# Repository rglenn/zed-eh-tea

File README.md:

# rg-rc2014
My own experiments in RC2014 hardware

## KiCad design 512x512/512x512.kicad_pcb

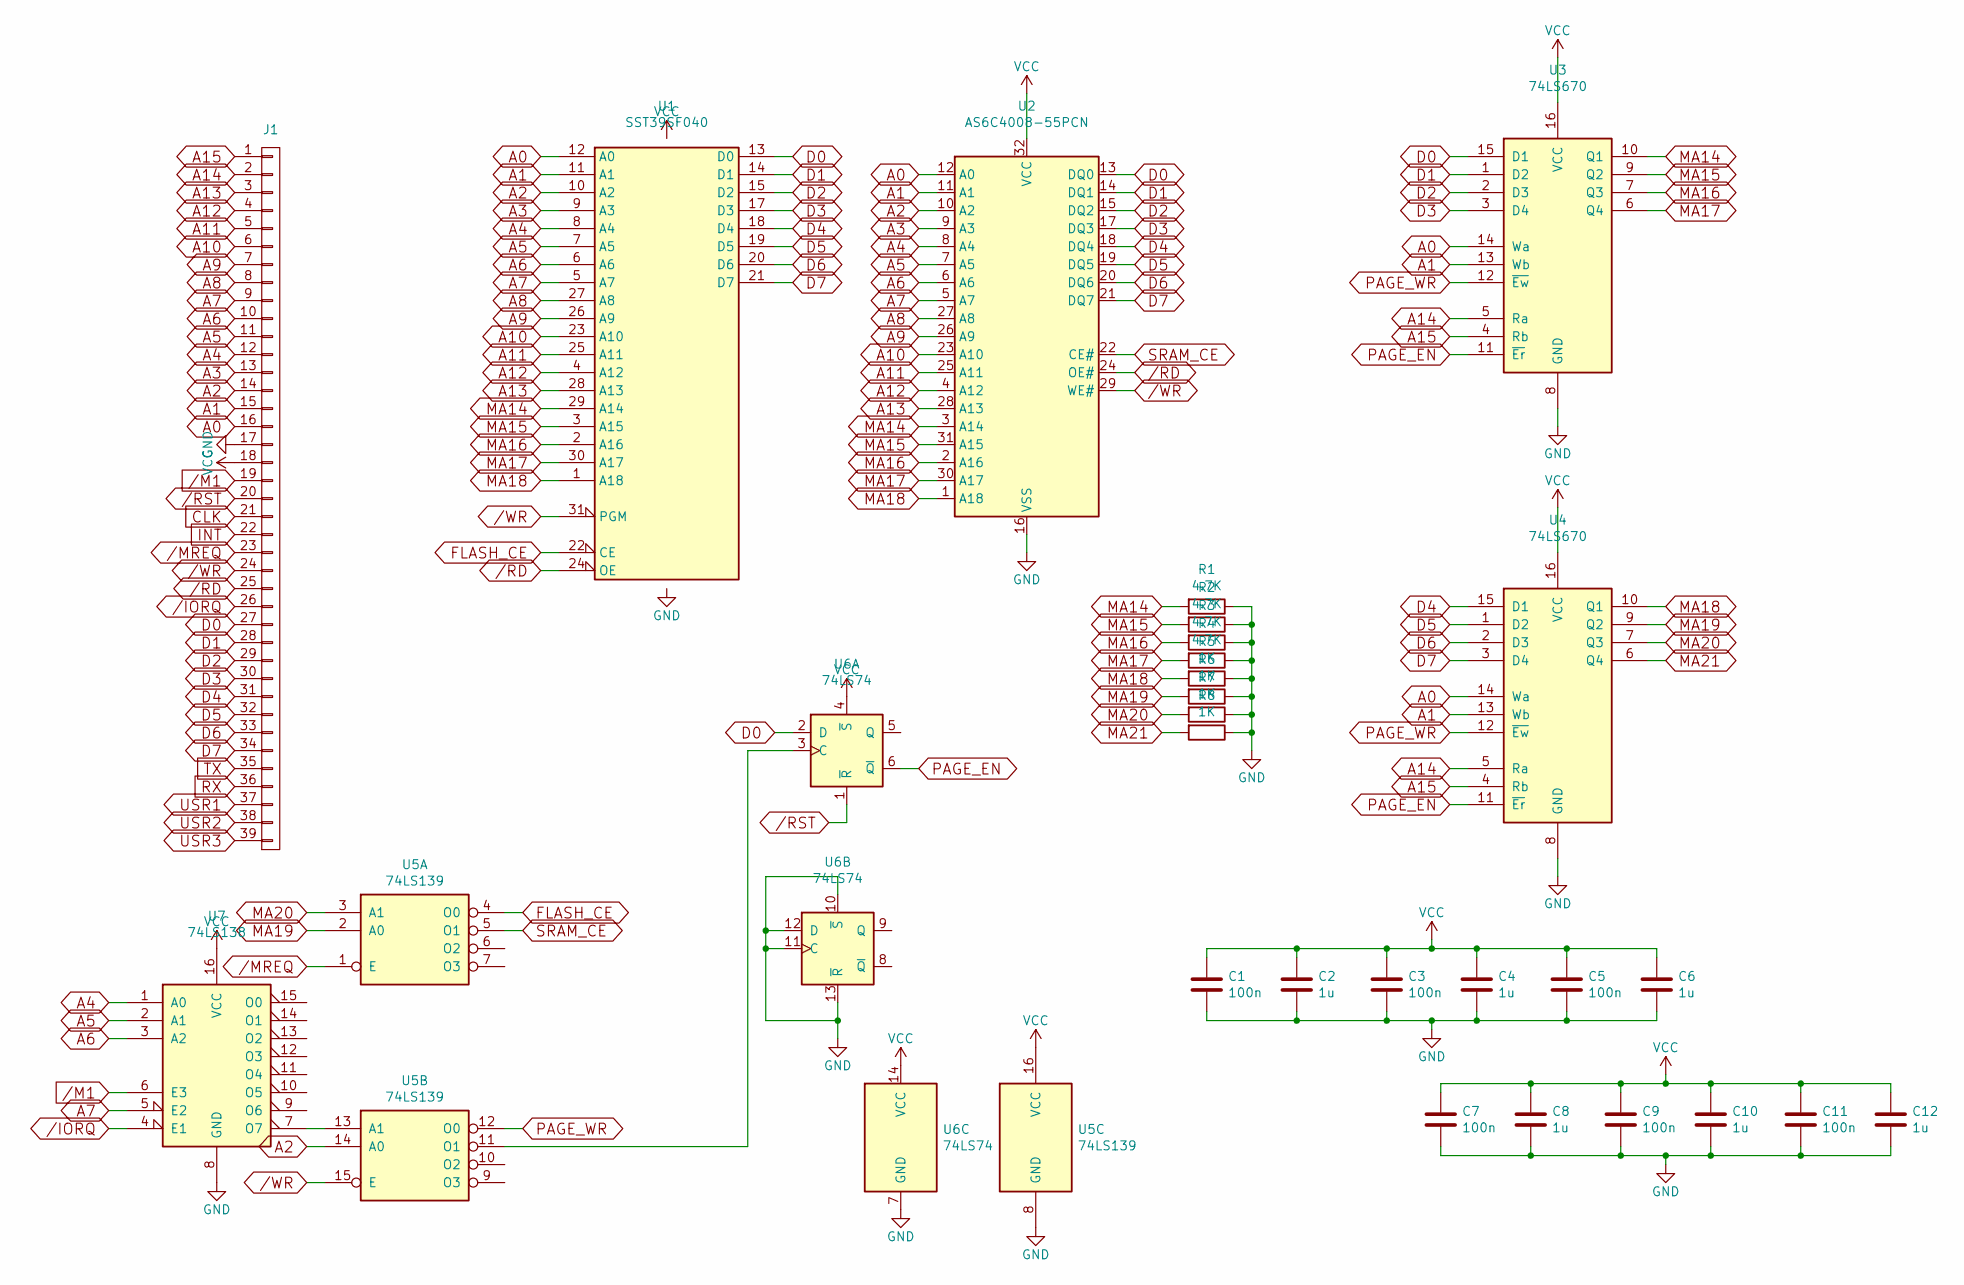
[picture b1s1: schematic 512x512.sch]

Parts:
C1, C3, C5, C7, C9, C11: 100n; C_0603_1608Metric
C2, C4, C6, C8, C10, C12: 1u; C_0603_1608Metric
J1: CONN_01X39; Pin_Header_Straight_1x39_Pitch2.54mm
R1, R2, R3, R4: 4.7K; R_Axial_DIN0204_L3.6mm_D1.6mm_P7.62mm_Horizontal
R5, R6, R7, R8: 1K; R_Axial_DIN0204_L3.6mm_D1.6mm_P7.62mm_Horizontal
U1: SST39SF040; DIP-32_W15.24mm
U2: AS6C4008-55PCN; DIP-32_W15.24mm
U3, U4: 74LS670; DIP-16_W7.62mm
U5: 74LS139; DIP-16_W7.62mm
U6: 74LS74; DIP-14_W7.62mm
U7: 74LS138; DIP-16_W7.62mm

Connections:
/IORQ: J1.26, U7.4 (E1)
/M1: J1.19, U7.6 (E3)
/MREQ: J1.23, U5.1 (E)
/RD: J1.25, U1.24 (OE), U2.24 (OE#)
/RST: J1.20, U6.1 (~R)
/WR: J1.24, U1.31 (PGM), U2.29 (WE#), U5.15 (E)
A0: J1.16, U1.12 (A0), U2.12 (A0), U3.14 (Wa), U4.14 (Wa)
A1: J1.15, U1.11 (A1), U2.11 (A1), U3.13 (Wb), U4.13 (Wb)
A2: J1.14, U1.10 (A2), U2.10 (A2), U5.14 (A0)
A3: J1.13, U1.9 (A3), U2.9 (A3)
A4: J1.12, U1.8 (A4), U2.8 (A4), U7.1 (A0)
A5: J1.11, U1.7 (A5), U2.7 (A5), U7.2 (A1)
A6: J1.10, U1.6 (A6), U2.6 (A6), U7.3 (A2)
A7: J1.9, U1.5 (A7), U2.5 (A7), U7.5 (E2)
A8: J1.8, U1.27 (A8), U2.27 (A8)
A9: J1.7, U1.26 (A9), U2.26 (A9)
A10: J1.6, U1.23 (A10), U2.23 (A10)
A11: J1.5, U1.25 (A11), U2.25 (A11)
A12: J1.4, U1.4 (A12), U2.4 (A12)
A13: J1.3, U1.28 (A13), U2.28 (A13)
A14: J1.2, U3.5 (Ra), U4.5 (Ra)
A15: J1.1, U3.4 (Rb), U4.4 (Rb)
CLK: J1.21
D0: J1.27, U1.13 (D0), U2.13 (DQ0), U3.15 (D1), U6.2 (D)
D1: J1.28, U1.14 (D1), U2.14 (DQ1), U3.1 (D2)
D2: J1.29, U1.15 (D2), U2.15 (DQ2), U3.2 (D3)
D3: J1.30, U1.17 (D3), U2.17 (DQ3), U3.3 (D4)
D4: J1.31, U1.18 (D4), U2.18 (DQ4), U4.15 (D1)
D5: J1.32, U1.19 (D5), U2.19 (DQ5), U4.1 (D2)
D6: J1.33, U1.20 (D6), U2.20 (DQ6), U4.2 (D3)
D7: J1.34, U1.21 (D7), U2.21 (DQ7), U4.3 (D4)
FLASH_CE: U1.22 (CE), U5.4 (O0)
GND: C1.2, C2.2, C3.2, C4.2, C5.2, C6.2, C7.2, C8.2, C9.2, C10.2, C11.2, C12.2, J1.17, R1.1, R2.1, R3.1, R4.1, R5.1, R6.1, R7.1, R8.1, U1.16 (GND), U2.16 (VSS), U3.8 (GND), U4.8 (GND), U5.8 (GND), U6.7 (GND), U6.10 (~S), U6.11 (C), U6.12 (D), U6.13 (~R), U7.8 (GND)
INT: J1.22
MA14: R1.2, U1.29 (A14), U2.3 (A14), U3.10 (Q1)
MA15: R2.2, U1.3 (A15), U2.31 (A15), U3.9 (Q2)
MA16: R3.2, U1.2 (A16), U2.2 (A16), U3.7 (Q3)
MA17: R4.2, U1.30 (A17), U2.30 (A17), U3.6 (Q4)
MA18: R5.2, U1.1 (A18), U2.1 (A18), U4.10 (Q1)
MA19: R6.2, U4.9 (Q2), U5.2 (A0)
MA20: R7.2, U4.7 (Q3), U5.3 (A1)
MA21: R8.2, U4.6 (Q4)
unnamed: U5.11 (O1), U6.3 (C)
unnamed: U5.13 (A1), U7.7 (O7)
PAGE_EN: U3.11 (~Er), U4.11 (~Er), U6.6 (~Q)
PAGE_WR: U3.12 (~Ew), U4.12 (~Ew), U5.12 (O0)
RX: J1.36
SRAM_CE: U2.22 (CE#), U5.5 (O1)
TX: J1.35
USR1: J1.37
USR2: J1.38
USR3: J1.39
VCC: C1.1, C2.1, C3.1, C4.1, C5.1, C6.1, C7.1, C8.1, C9.1, C10.1, C11.1, C12.1, J1.18, U1.32 (VCC), U2.32 (VCC), U3.16 (VCC), U4.16 (VCC), U5.16 (VCC), U6.4 (~S), U6.14 (VCC), U7.16 (VCC)

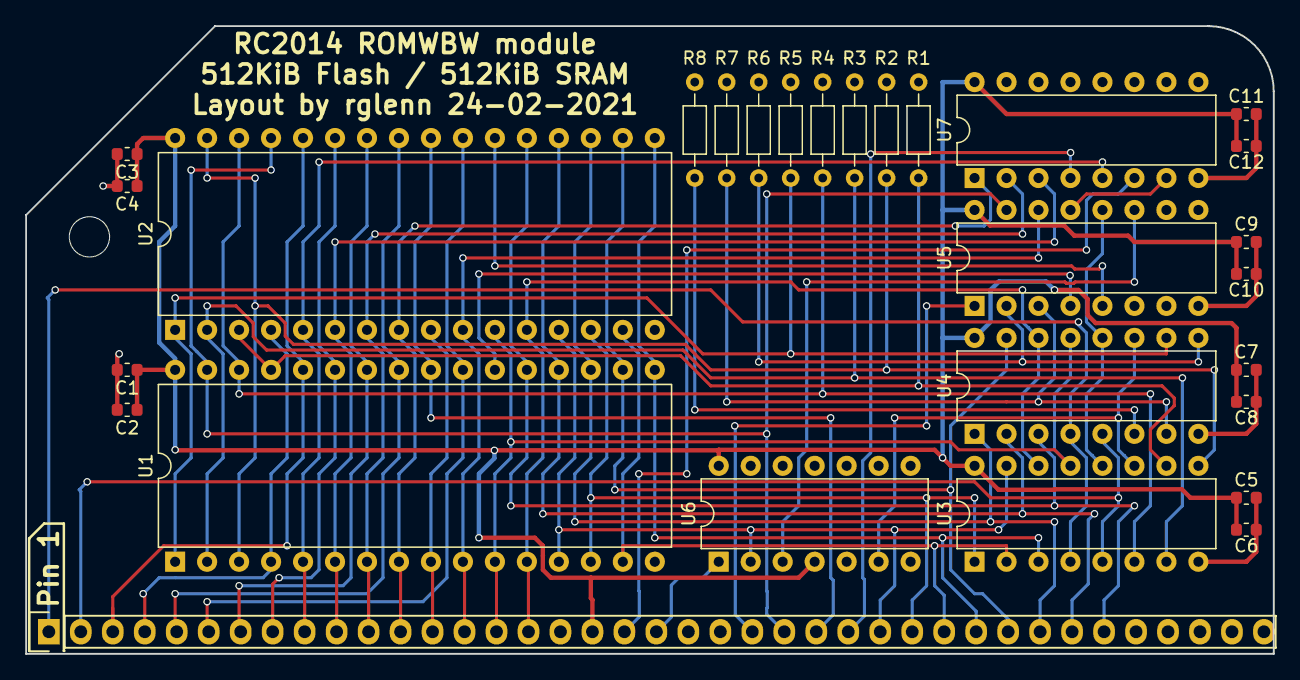
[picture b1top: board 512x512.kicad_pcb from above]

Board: 2 copper layers, 99.1 x 49.9 mm, 29 parts (0 on the bottom side), 46 nets.

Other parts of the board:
MNT0: MountingHole_3.2mm_M3

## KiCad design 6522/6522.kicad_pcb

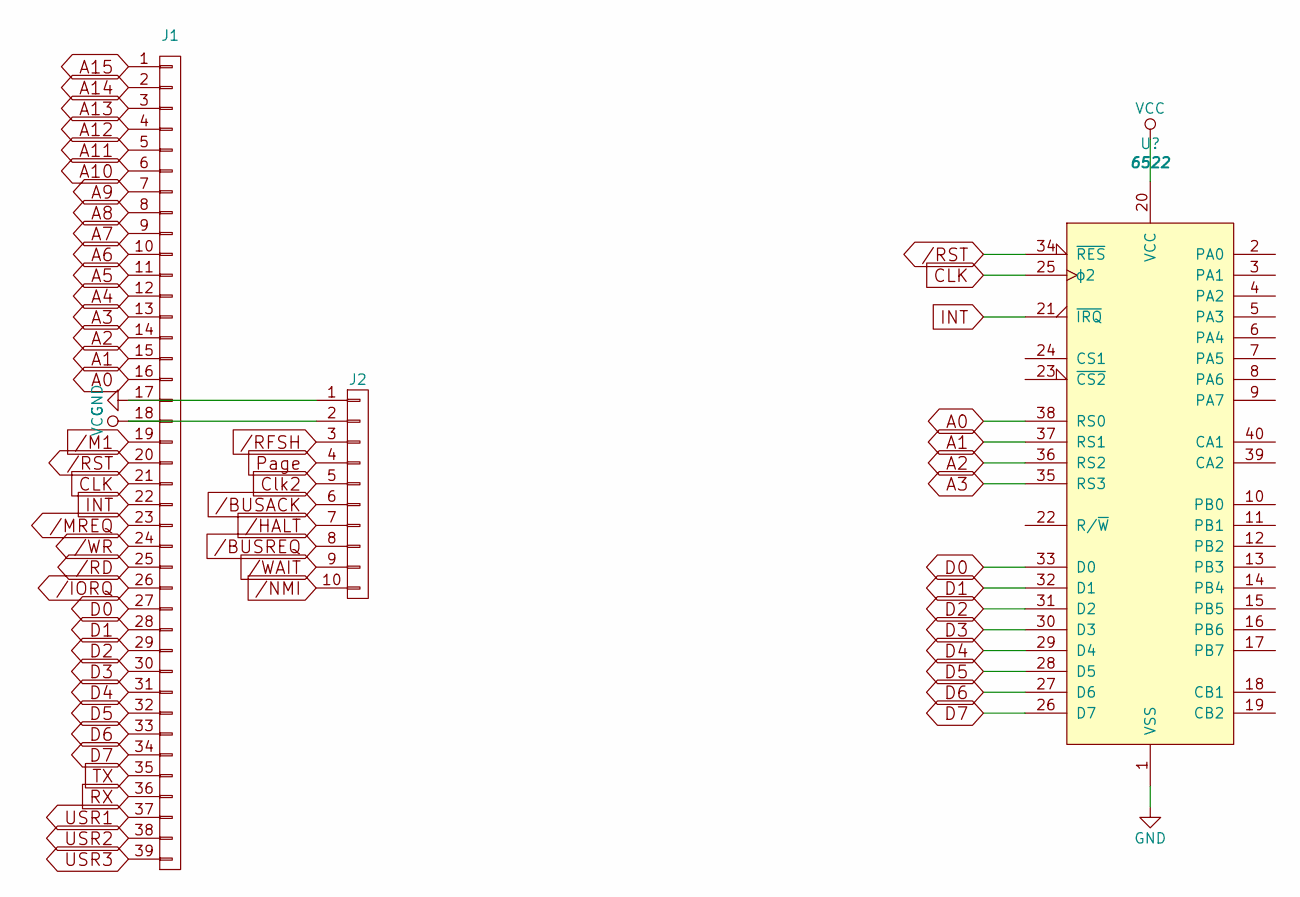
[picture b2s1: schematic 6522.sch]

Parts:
J1: CONN_01X39; Pin_Header_Straight_1x39_Pitch2.54mm
J2: CONN_01X10; Pin_Header_Straight_1x10_Pitch2.54mm

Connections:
/BUSACK: J2.6
/BUSREQ: J2.8
/HALT: J2.7
/IORQ: J1.26
/M1: J1.19
/MREQ: J1.23
/NMI: J2.10
/RD: J1.25
/RFSH: J2.3
/RST: J1.20
/WAIT: J2.9
/WR: J1.24
A0: J1.16
A1: J1.15
A2: J1.14
A3: J1.13
A4: J1.12
A5: J1.11
A6: J1.10
A7: J1.9
A8: J1.8
A9: J1.7
A10: J1.6
A11: J1.5
A12: J1.4
A13: J1.3
A14: J1.2
A15: J1.1
CLK: J1.21
Clk2: J2.5
D0: J1.27
D1: J1.28
D2: J1.29
D3: J1.30
D4: J1.31
D5: J1.32
D6: J1.33
D7: J1.34
GND: J1.17, J2.1
INT: J1.22
Page: J2.4
RX: J1.36
TX: J1.35
USR1: J1.37
USR2: J1.38
USR3: J1.39
VCC: J1.18, J2.2

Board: 2 copper layers, 3 parts (0 on the bottom side), 2 nets, no tracks yet.

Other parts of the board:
MNT0: MountingHole_3.2mm_M3

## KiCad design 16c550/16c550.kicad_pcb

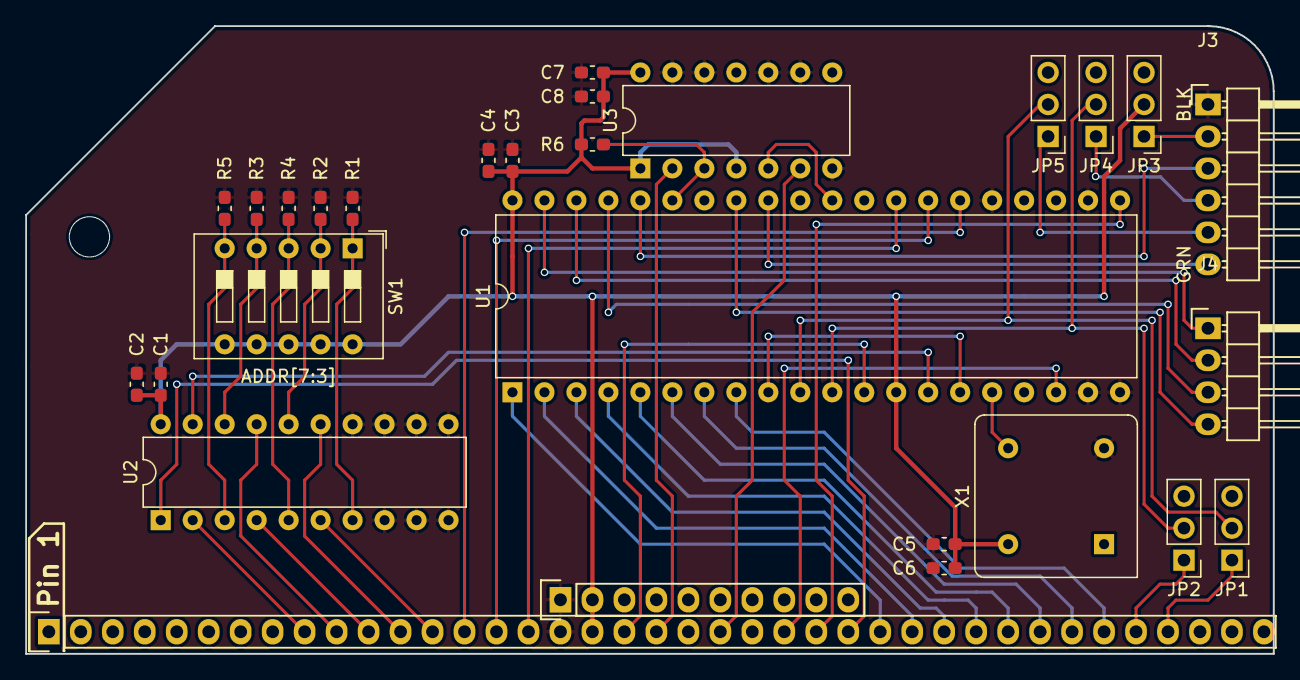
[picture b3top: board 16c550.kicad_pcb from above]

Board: 2 copper layers, 99.1 x 49.9 mm, 29 parts (0 on the bottom side), 47 nets.

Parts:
C1, C3, C5, C7: 100n; C_0603_1608Metric_Pad1.05x0.95mm_HandSolder
C2, C4, C6, C8: 1u; C_0603_1608Metric_Pad1.05x0.95mm_HandSolder
J1: CONN_01X39; Pin_Header_Straight_1x39_Pitch2.54mm
J2: CONN_01X10; Pin_Header_Straight_1x10_Pitch2.54mm
J3: Conn_01x06; Pin_Header_Angled_1x06
J4: Conn_01x04; Pin_Header_Angled_1x04
JP1, JP2, JP3, JP4, JP5: Jumper_3_Open; Pin_Header_Straight_1x03_Pitch2.54mm
MNT0: MountingHole_3.2mm_M3
R1, R2, R3, R4, R5, R6: 10k; R_0603_1608Metric_Pad1.05x0.95mm_HandSolder
SW1: SW_DIP_x05; SW_DIP_SPSTx05_Slide_9.78x14.88mm_W7.62mm_P2.54mm
U1: 16550; DIP-40_W15.24mm
U2: 74LS688; DIP-20_W7.62mm
U3: 74LS03; DIP-14_W7.62mm
X1: CXO_DIP8; Oscillator_DIP-8

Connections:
/IORQ: J1.26, U2.1
/M1: J1.19, U1.12
/RD: J1.25, U1.21
/RST: J1.20, U3.2
/UART_CLK: U1.16, X1.5
/UART_CS: U1.14, U2.19
/UART_INT: U1.30, U3.5
/UART_RST: R6.2, U1.35, U3.3
/UART_RX: JP1.2, JP5.2, U1.10
/UART_TX: JP2.2, JP4.2, U1.11
/WR: J1.24, U1.18
/~CTS: J3.3, U1.36
/~DCD: J4.2, U1.38
/~DSR: J4.3, U1.37
/~DTR: J4.4, U1.33
/~RI: J4.1, U1.39
/~RTS: J3.6, U1.32
A0: J1.16, U1.28
A1: J1.15, U1.27
A2: J1.14, U1.26
A3: J1.13, U2.6
A4: J1.12, U2.15
A5: J1.11, U2.4
A6: J1.10, U2.17
A7: J1.9, U2.2
D0: J1.27, U1.1
D1: J1.28, U1.2
D2: J1.29, U1.3
D3: J1.30, U1.4
D4: J1.31, U1.5
D5: J1.32, U1.6
D6: J1.33, U1.7
D7: J1.34, U1.8
GND: C1.2, C2.2, C3.2, C4.2, C5.2, C6.2, C7.2, C8.2, J1.17, J2.1, J3.1, R1.2, R2.2, R3.2, R4.2, R5.2, U1.19, U1.20, U1.22, U1.25, U2.8, U2.9, U2.10, U2.11, U2.12, U2.13, U2.14, U3.7, U3.9, U3.10, U3.12, U3.13, X1.4
INT: J1.22, U3.6
unnamed: J3.2, JP3.1
unnamed: J3.4, JP4.1
unnamed: J3.5, JP5.1
unnamed: R1.1, SW1.1, U2.7
unnamed: R2.1, SW1.2, U2.16
unnamed: R3.1, SW1.4, U2.18
unnamed: R4.1, SW1.3, U2.5
unnamed: R5.1, SW1.5, U2.3
unnamed: U1.9, U1.15
RX: J1.36, JP1.1
TX: J1.35, JP2.1
VCC: C1.1, C2.1, C3.1, C4.1, C5.1, C6.1, C7.1, C8.1, J1.18, J2.2, JP3.2, R6.1, SW1.6, SW1.7, SW1.8, SW1.9, SW1.10, U1.13, U1.40, U2.20, U3.1, U3.4, U3.14, X1.8

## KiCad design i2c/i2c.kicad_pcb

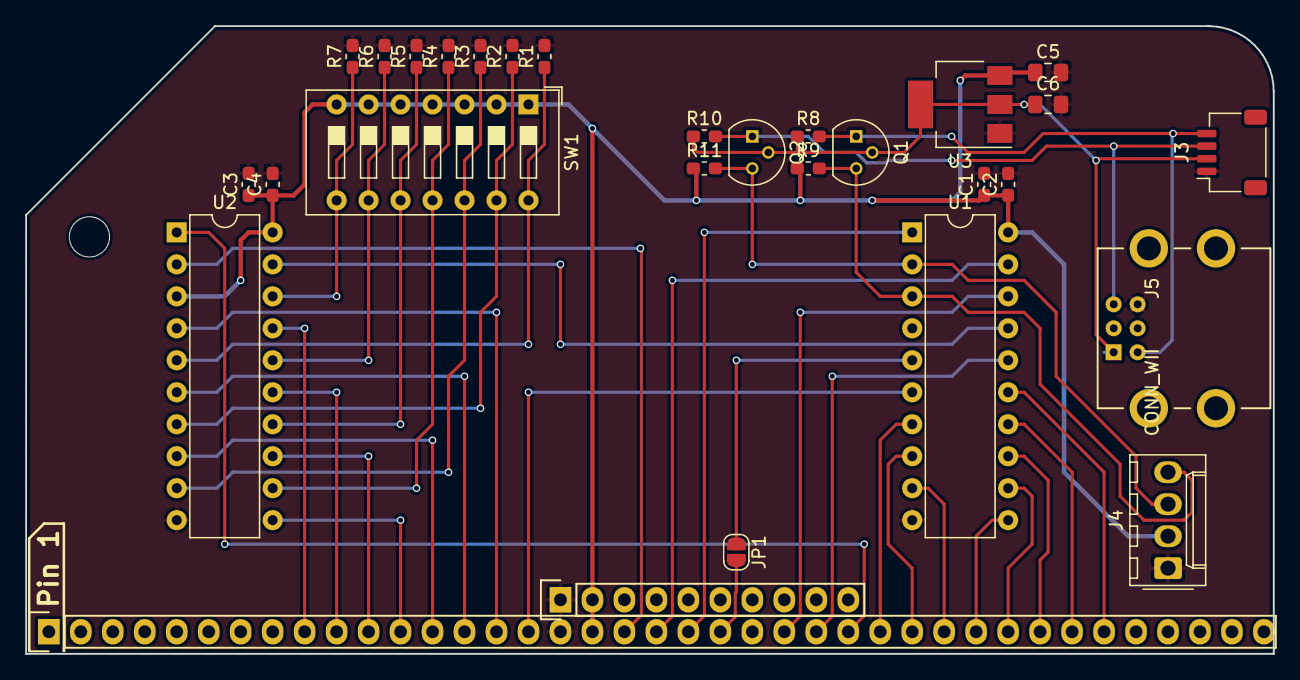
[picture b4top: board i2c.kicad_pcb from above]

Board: 2 copper layers, 99.1 x 49.9 mm, 30 parts (0 on the bottom side), 39 nets.

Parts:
C1, C3: 1u; R_0603_1608Metric_Pad1.05x0.95mm_HandSolder
C2, C4: 100n; R_0603_1608Metric_Pad1.05x0.95mm_HandSolder
C5, C6: 10u; R_0805_2012Metric_Pad1.15x1.40mm_HandSolder
J1: CONN_01X39; Pin_Header_Straight_1x39_Pitch2.54mm
J2: CONN_01X10; Pin_Header_Straight_1x10_Pitch2.54mm
J3: Conn_01x04; JST_SH_SM04B-SRSS-TB_1x04-1MP_P1.00mm_Horizontal
J4: Conn_01x04; Molex_KK-254_AE-6410-04A_1x04_P2.54mm_Vertical
J5: CONN_WII
JP1: SolderJumper_2_Open; SolderJumper-2_P1.3mm_Open_RoundedPad1.0x1.5mm
MNT0: MountingHole_3.2mm_M3
Q1, Q2: 2N7000; TO-92_Molded_Narrow
R1, R2, R3, R4, R5, R6, R7: 10K; R_0603_1608Metric_Pad1.05x0.95mm_HandSolder
R8, R9, R10, R11: 4.7K; R_0603_1608Metric_Pad1.05x0.95mm_HandSolder
SW1: SW_DIP_x07; SW_DIP_SPSTx07_Slide_9.78x19.96mm_W7.62mm_P2.54mm
U1: PCF8584; DIP-20_W7.62mm
U2: 74LS688; DIP-20_W7.62mm
U3: AP1117-33; SOT-223-3Lead_TabPin2

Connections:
+3V3: C6.1, J3.2, J5.1, Q1.2, Q2.2, R8.1, R10.1, U3.2
/IORQ: J1.26, U2.1
/M1: J1.19, U2.2
/RD: J1.25, U1.16
/RST: J1.20, U1.19
/SCL_3.3: J3.4, J5.2, Q1.1, R8.2
/SCL_5: J4.4, Q1.3, R9.2, U1.3
/SDA_3.3: J3.3, J5.5, Q2.1, R10.2
/SDA_5: J4.3, Q2.3, R11.2, U1.2
/WR: J1.24, U1.18
/~CS: U1.17, U2.19
A0: J1.16, U1.6
A1: J1.15, U2.4
A2: J1.14, U2.6
A3: J1.13, U2.8
A4: J1.12, U2.11
A5: J1.11, U2.13
A6: J1.10, U2.15
A7: J1.9, U2.17
CLK: J1.21, U1.1
D0: J1.27, U1.7
D1: J1.28, U1.8
D2: J1.29, U1.9
D3: J1.30, U1.11
D4: J1.31, U1.12
D5: J1.32, U1.13
D6: J1.33, U1.14
D7: J1.34, U1.15
GND: C1.2, C2.2, C3.2, C4.2, C5.2, C6.2, J1.17, J2.1, J3.1, J4.1, J5.6, R1.2, R2.2, R3.2, R4.2, R5.2, R6.2, R7.2, U1.10, U2.10, U3.1
INT: J1.22, JP1.2
unnamed: JP1.1, U1.5
unnamed: R1.1, SW1.14, U2.5
unnamed: R2.1, SW1.13, U2.7
unnamed: R3.1, SW1.12, U2.9
unnamed: R4.1, SW1.11, U2.12
unnamed: R5.1, SW1.10, U2.14
unnamed: R6.1, SW1.9, U2.16
unnamed: R7.1, SW1.8, U2.18
VCC: C1.1, C2.1, C3.1, C4.1, C5.1, J1.18, J2.2, J4.2, R9.1, R11.1, SW1.1, SW1.2, SW1.3, SW1.4, SW1.5, SW1.6, SW1.7, U1.20, U2.3, U2.20, U3.3

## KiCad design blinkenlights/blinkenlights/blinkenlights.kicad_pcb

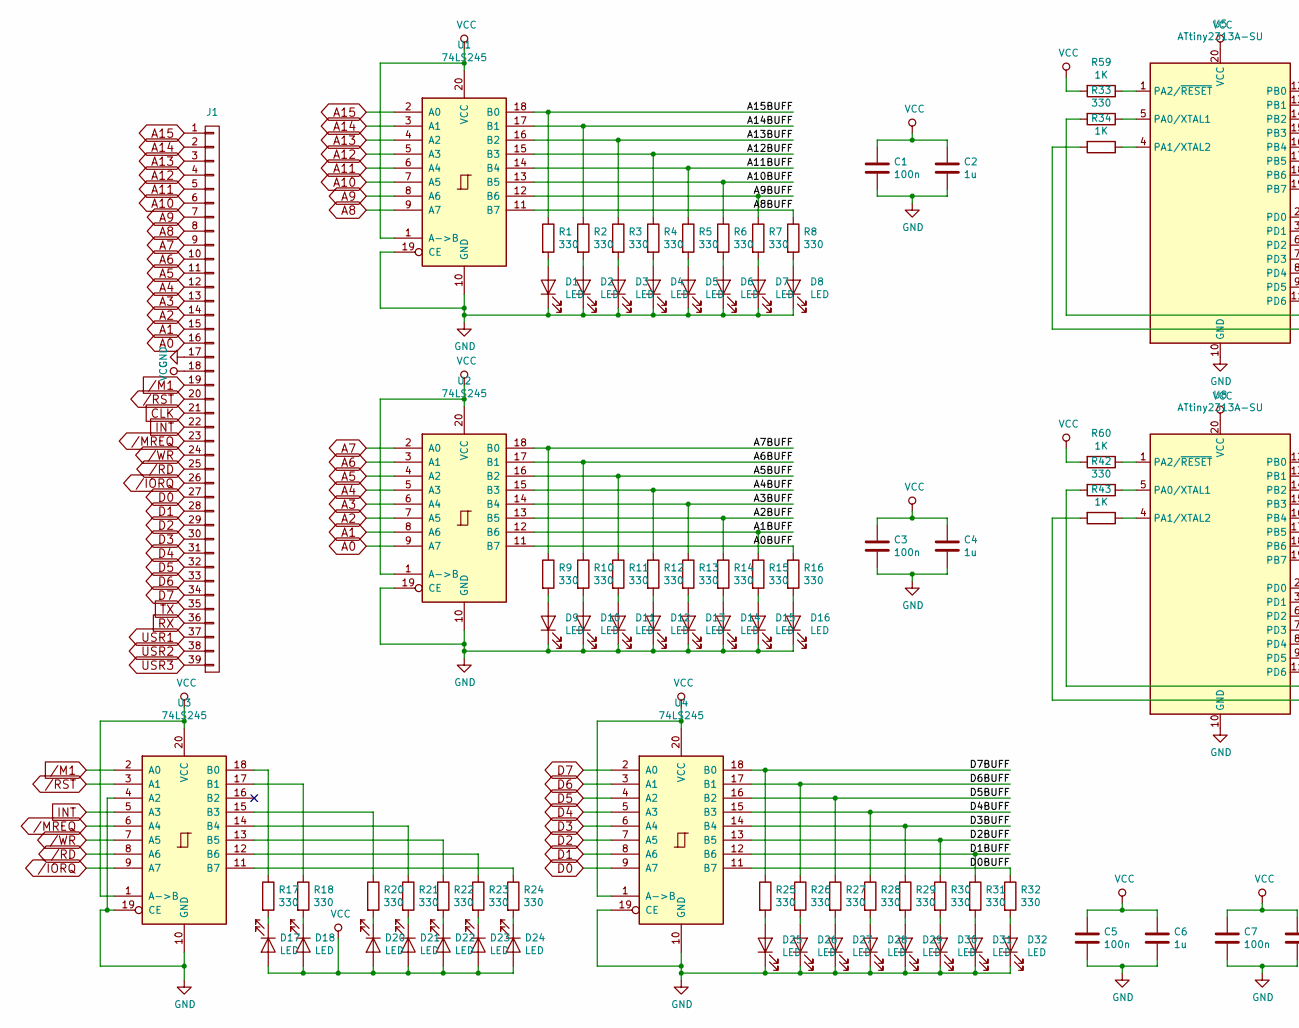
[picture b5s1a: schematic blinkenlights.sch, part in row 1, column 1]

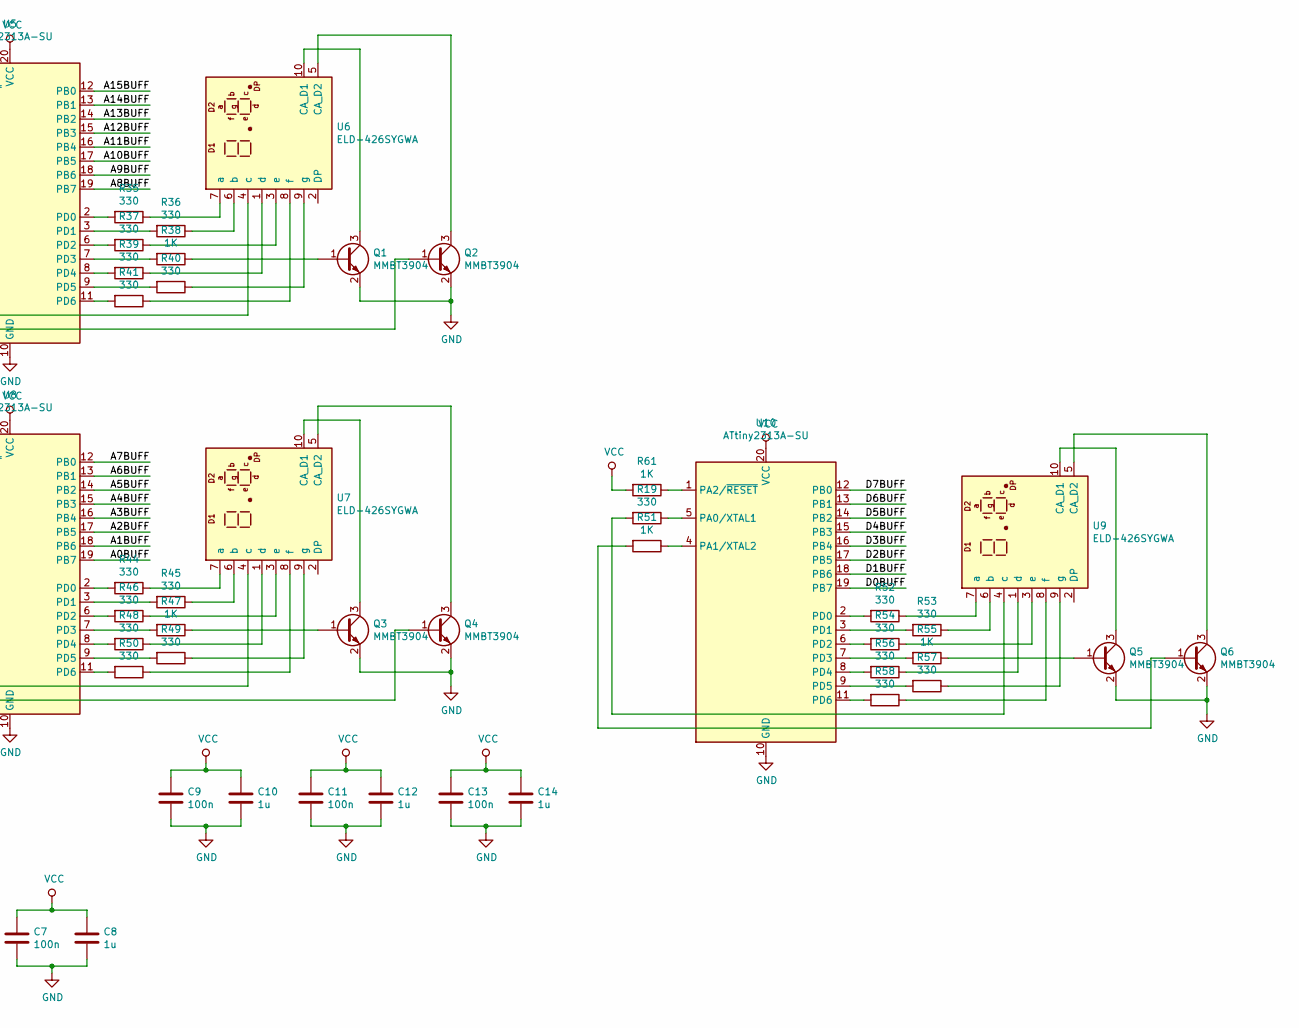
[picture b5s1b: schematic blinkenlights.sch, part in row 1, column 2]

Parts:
C1, C3, C5, C7, C9, C11, C13: 100n; C_0603_1608Metric_Pad1.05x0.95mm_HandSolder
C2, C4, C6, C8, C10, C12, C14: 1u; C_0603_1608Metric_Pad1.05x0.95mm_HandSolder
D1, D2, D3, D4, D5, D6, D7, D8, D9, D10, D11, D12, D13, D14, D15, D16, D17, D18, D20, D21, D22, D23, D24, D25, D26, D27, D28, D29, D30, D31, D32: LED; LED_Rectangular_W5.0mm_H2.0mm
J1: CONN_01X39; Pin_Header_Straight_1x39_Pitch2.54mm
Q1, Q2, Q3, Q4, Q5, Q6: MMBT3904; SOT-23
R1, R2, R3, R4, R5, R6, R7, R8, R9, R10, R11, R12, R13, R14, R15, R16, R17, R18, R19, R20, R21, R22, R23, R24, R25, R26, R27, R28, R29, R30, R31, R32, R33, R35, R36, R37, R39, R40, R41, R42, R44, R45, R46, R48, R49, R50, R52, R53, R54, R56, R57, R58: 330; R_0603_1608Metric_Pad1.05x0.95mm_HandSolder
R34, R38, R43, R47, R51, R55, R59, R60, R61: 1K; R_0603_1608Metric_Pad1.05x0.95mm_HandSolder
U1, U2, U3, U4: 74LS245; SOIC-20W_7.5x12.8mm_Pitch1.27mm
U5, U8, U10: ATtiny2313A-SU; SOIC-20W_7.5x12.8mm_P1.27mm
U6, U7, U9: ELD-426SYGWA; ELD_426XXXX

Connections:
/A0BUFF: R16.1, U2.11 (B7), U8.19 (PB7)
/A1BUFF: R15.1, U2.12 (B6), U8.18 (PB6)
/A2BUFF: R14.1, U2.13 (B5), U8.17 (PB5)
/A3BUFF: R13.1, U2.14 (B4), U8.16 (PB4)
/A4BUFF: R12.1, U2.15 (B3), U8.15 (PB3)
/A5BUFF: R11.1, U2.16 (B2), U8.14 (PB2)
/A6BUFF: R10.1, U2.17 (B1), U8.13 (PB1)
/A7BUFF: R9.1, U2.18 (B0), U8.12 (PB0)
/A8BUFF: R8.1, U1.11 (B7), U5.19 (PB7)
/A9BUFF: R7.1, U1.12 (B6), U5.18 (PB6)
/A10BUFF: R6.1, U1.13 (B5), U5.17 (PB5)
/A11BUFF: R5.1, U1.14 (B4), U5.16 (PB4)
/A12BUFF: R4.1, U1.15 (B3), U5.15 (PB3)
/A13BUFF: R3.1, U1.16 (B2), U5.14 (PB2)
/A14BUFF: R2.1, U1.17 (B1), U5.13 (PB1)
/A15BUFF: R1.1, U1.18 (B0), U5.12 (PB0)
/D0BUFF: R32.1, U4.11 (B7), U10.19 (PB7)
/D1BUFF: R31.1, U4.12 (B6), U10.18 (PB6)
/D2BUFF: R30.1, U4.13 (B5), U10.17 (PB5)
/D3BUFF: R29.1, U4.14 (B4), U10.16 (PB4)
/D4BUFF: R28.1, U4.15 (B3), U10.15 (PB3)
/D5BUFF: R27.1, U4.16 (B2), U10.14 (PB2)
/D6BUFF: R26.1, U4.17 (B1), U10.13 (PB1)
/D7BUFF: R25.1, U4.18 (B0), U10.12 (PB0)
/IORQ: J1.26, U3.9 (A7)
/M1: J1.19, U3.2 (A0)
/MREQ: J1.23, U3.6 (A4)
/RD: J1.25, U3.8 (A6)
/RST: J1.20, U3.3 (A1)
/WR: J1.24, U3.7 (A5)
A0: J1.16, U2.9 (A7)
A1: J1.15, U2.8 (A6)
A2: J1.14, U2.7 (A5)
A3: J1.13, U2.6 (A4)
A4: J1.12, U2.5 (A3)
A5: J1.11, U2.4 (A2)
A6: J1.10, U2.3 (A1)
A7: J1.9, U2.2 (A0)
A8: J1.8, U1.9 (A7)
A9: J1.7, U1.8 (A6)
A10: J1.6, U1.7 (A5)
A11: J1.5, U1.6 (A4)
A12: J1.4, U1.5 (A3)
A13: J1.3, U1.4 (A2)
A14: J1.2, U1.3 (A1)
A15: J1.1, U1.2 (A0)
D0: J1.27, U4.9 (A7)
D1: J1.28, U4.8 (A6)
D2: J1.29, U4.7 (A5)
D3: J1.30, U4.6 (A4)
D4: J1.31, U4.5 (A3)
D5: J1.32, U4.4 (A2)
D6: J1.33, U4.3 (A1)
D7: J1.34, U4.2 (A0)
GND: C1.2, C2.2, C3.2, C4.2, C5.2, C6.2, C7.2, C8.2, C9.2, C10.2, C11.2, C12.2, C13.2, C14.2, D1.1 (K), D2.1 (K), D3.1 (K), D4.1 (K), D5.1 (K), D6.1 (K), D7.1 (K), D8.1 (K), D9.1 (K), D10.1 (K), D11.1 (K), D12.1 (K), D13.1 (K), D14.1 (K), D15.1 (K), D16.1 (K), D25.1 (K), D26.1 (K), D27.1 (K), D28.1 (K), D29.1 (K), D30.1 (K), D31.1 (K), D32.1 (K), J1.17, Q1.2 (E), Q2.2 (E), Q3.2 (E), Q4.2 (E), Q5.2 (E), Q6.2 (E), U1.10 (GND), U1.19 (CE), U2.10 (GND), U2.19 (CE), U3.4 (A2), U3.10 (GND), U3.19 (CE), U4.10 (GND), U4.19 (CE), U5.10 (GND), U8.10 (GND), U10.10 (GND)
INT: J1.22, U3.5 (A3)
unnamed: D1.2 (A), R1.2
unnamed: D2.2 (A), R2.2
unnamed: D3.2 (A), R3.2
unnamed: D4.2 (A), R4.2
unnamed: D5.2 (A), R5.2
unnamed: D6.2 (A), R6.2
unnamed: D7.2 (A), R7.2
unnamed: D8.2 (A), R8.2
unnamed: D9.2 (A), R9.2
unnamed: D10.2 (A), R10.2
unnamed: D11.2 (A), R11.2
unnamed: D12.2 (A), R12.2
unnamed: D13.2 (A), R13.2
unnamed: D14.2 (A), R14.2
unnamed: D15.2 (A), R15.2
unnamed: D16.2 (A), R16.2
unnamed: D17.1 (K), R17.2
unnamed: D18.1 (K), R18.2
unnamed: D20.1 (K), R20.2
unnamed: D21.1 (K), R21.2
unnamed: D22.1 (K), R22.2
unnamed: D23.1 (K), R23.2
unnamed: D24.1 (K), R24.2
unnamed: D25.2 (A), R25.2
unnamed: D26.2 (A), R26.2
unnamed: D27.2 (A), R27.2
unnamed: D28.2 (A), R28.2
unnamed: D29.2 (A), R29.2
unnamed: D30.2 (A), R30.2
unnamed: D31.2 (A), R31.2
unnamed: D32.2 (A), R32.2
unnamed: Q1.1 (B), R38.1
unnamed: Q1.3 (C), U6.10 (CA_D1)
unnamed: Q2.1 (B), R34.2
unnamed: Q2.3 (C), U6.5 (CA_D2)
unnamed: Q3.1 (B), R47.1
unnamed: Q3.3 (C), U7.10 (CA_D1)
unnamed: Q4.1 (B), R43.2
unnamed: Q4.3 (C), U7.5 (CA_D2)
unnamed: Q5.1 (B), R55.1
unnamed: Q5.3 (C), U9.10 (CA_D1)
unnamed: Q6.1 (B), R51.2
unnamed: Q6.3 (C), U9.5 (CA_D2)
unnamed: R17.1, U3.18 (B0)
unnamed: R18.1, U3.17 (B1)
unnamed: R19.1, U10.5 (PA0/XTAL1)
unnamed: R19.2, U9.4 (c)
unnamed: R20.1, U3.15 (B3)
unnamed: R21.1, U3.14 (B4)
unnamed: R22.1, U3.13 (B5)
unnamed: R23.1, U3.12 (B6)
unnamed: R24.1, U3.11 (B7)
unnamed: R33.1, U5.5 (PA0/XTAL1)
unnamed: R33.2, U6.4 (c)
unnamed: R34.1, U5.4 (PA1/XTAL2)
unnamed: R35.1, U6.7 (a)
unnamed: R35.2, U5.2 (PD0)
unnamed: R36.1, U6.6 (b)
unnamed: R36.2, U5.3 (PD1)
unnamed: R37.1, U6.3 (e)
unnamed: R37.2, U5.6 (PD2)
unnamed: R38.2, U5.7 (PD3)
unnamed: R39.1, U6.1 (d)
unnamed: R39.2, U5.8 (PD4)
unnamed: R40.1, U6.9 (g)
unnamed: R40.2, U5.9 (PD5)
unnamed: R41.1, U6.8 (f)
unnamed: R41.2, U5.11 (PD6)
unnamed: R42.1, U8.5 (PA0/XTAL1)
unnamed: R42.2, U7.4 (c)
unnamed: R43.1, U8.4 (PA1/XTAL2)
unnamed: R44.1, U7.7 (a)
unnamed: R44.2, U8.2 (PD0)
unnamed: R45.1, U7.6 (b)
unnamed: R45.2, U8.3 (PD1)
unnamed: R46.1, U7.3 (e)
unnamed: R46.2, U8.6 (PD2)
unnamed: R47.2, U8.7 (PD3)
unnamed: R48.1, U7.1 (d)
unnamed: R48.2, U8.8 (PD4)
unnamed: R49.1, U7.9 (g)
unnamed: R49.2, U8.9 (PD5)
unnamed: R50.1, U7.8 (f)
unnamed: R50.2, U8.11 (PD6)
unnamed: R51.1, U10.4 (PA1/XTAL2)
unnamed: R52.1, U9.7 (a)
unnamed: R52.2, U10.2 (PD0)
unnamed: R53.1, U9.6 (b)
unnamed: R53.2, U10.3 (PD1)
unnamed: R54.1, U9.3 (e)
unnamed: R54.2, U10.6 (PD2)
unnamed: R55.2, U10.7 (PD3)
unnamed: R56.1, U9.1 (d)
unnamed: R56.2, U10.8 (PD4)
unnamed: R57.1, U9.9 (g)
unnamed: R57.2, U10.9 (PD5)
unnamed: R58.1, U9.8 (f)
unnamed: R58.2, U10.11 (PD6)
unnamed: R59.1, U5.1 (PA2/~RESET)
unnamed: R60.1, U8.1 (PA2/~RESET)
unnamed: R61.1, U10.1 (PA2/~RESET)
VCC: C1.1, C2.1, C3.1, C4.1, C5.1, C6.1, C7.1, C8.1, C9.1, C10.1, C11.1, C12.1, C13.1, C14.1, D17.2 (A), D18.2 (A), D20.2 (A), D21.2 (A), D22.2 (A), D23.2 (A), D24.2 (A), J1.18, R59.2, R60.2, R61.2, U1.1 (A->B), U1.20 (VCC), U2.1 (A->B), U2.20 (VCC), U3.1 (A->B), U3.20 (VCC), U4.1 (A->B), U4.20 (VCC), U5.20 (VCC), U8.20 (VCC), U10.20 (VCC)

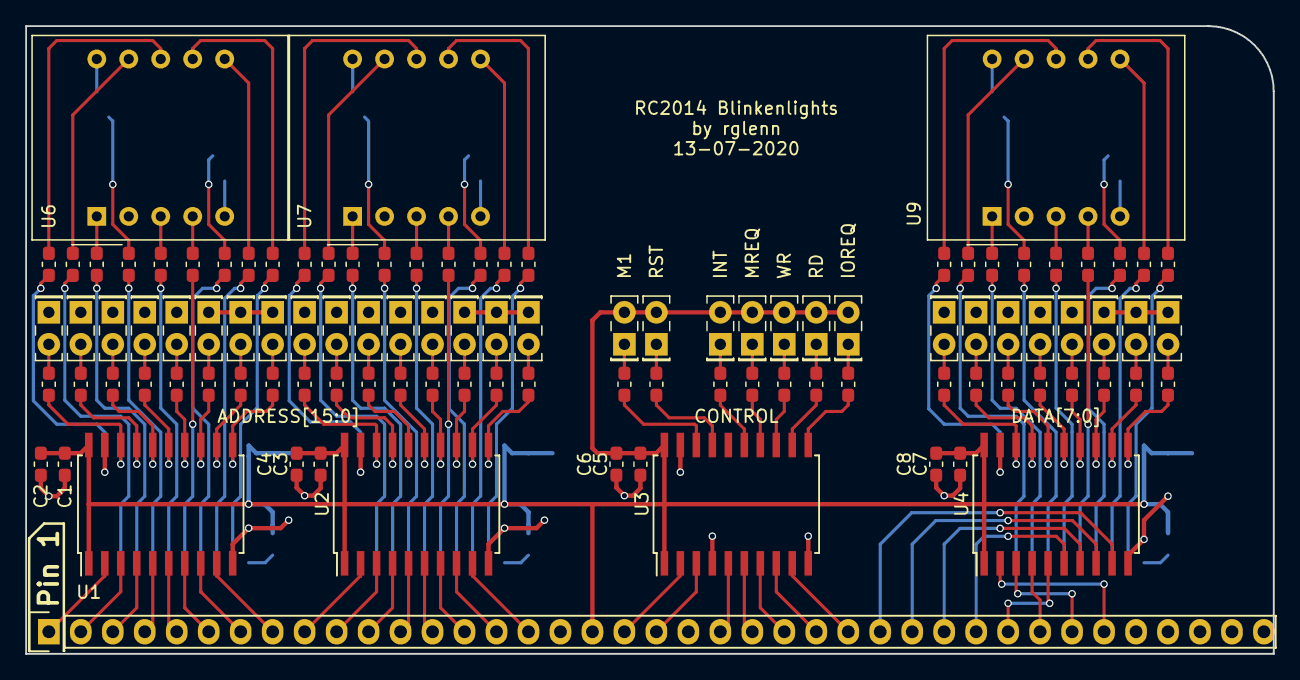
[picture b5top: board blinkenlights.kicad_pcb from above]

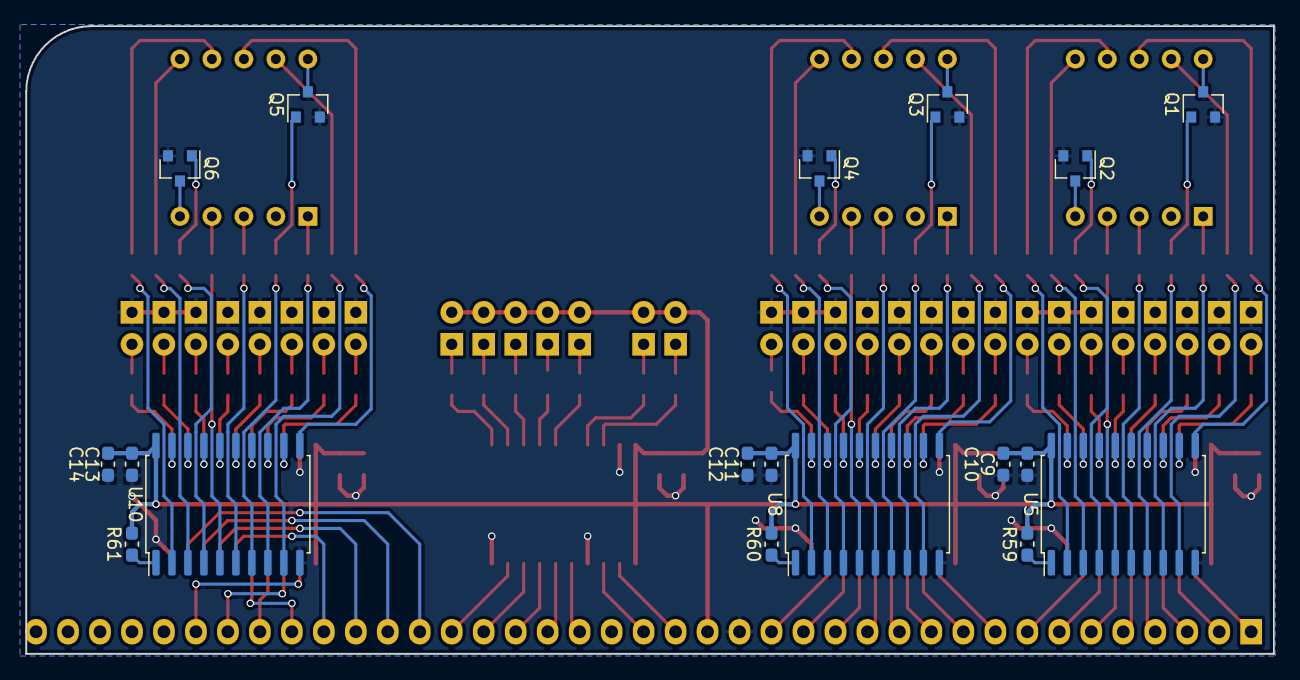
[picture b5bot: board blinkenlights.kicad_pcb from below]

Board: 2 copper layers, 99.1 x 49.9 mm, 123 parts (18 on the bottom side), 158 nets.
